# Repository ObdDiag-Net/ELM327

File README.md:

ELM327 adapter and firmware based on PIC18F25K80
==========================================

See http://www.obddiag.net/elm327.html project page for details.

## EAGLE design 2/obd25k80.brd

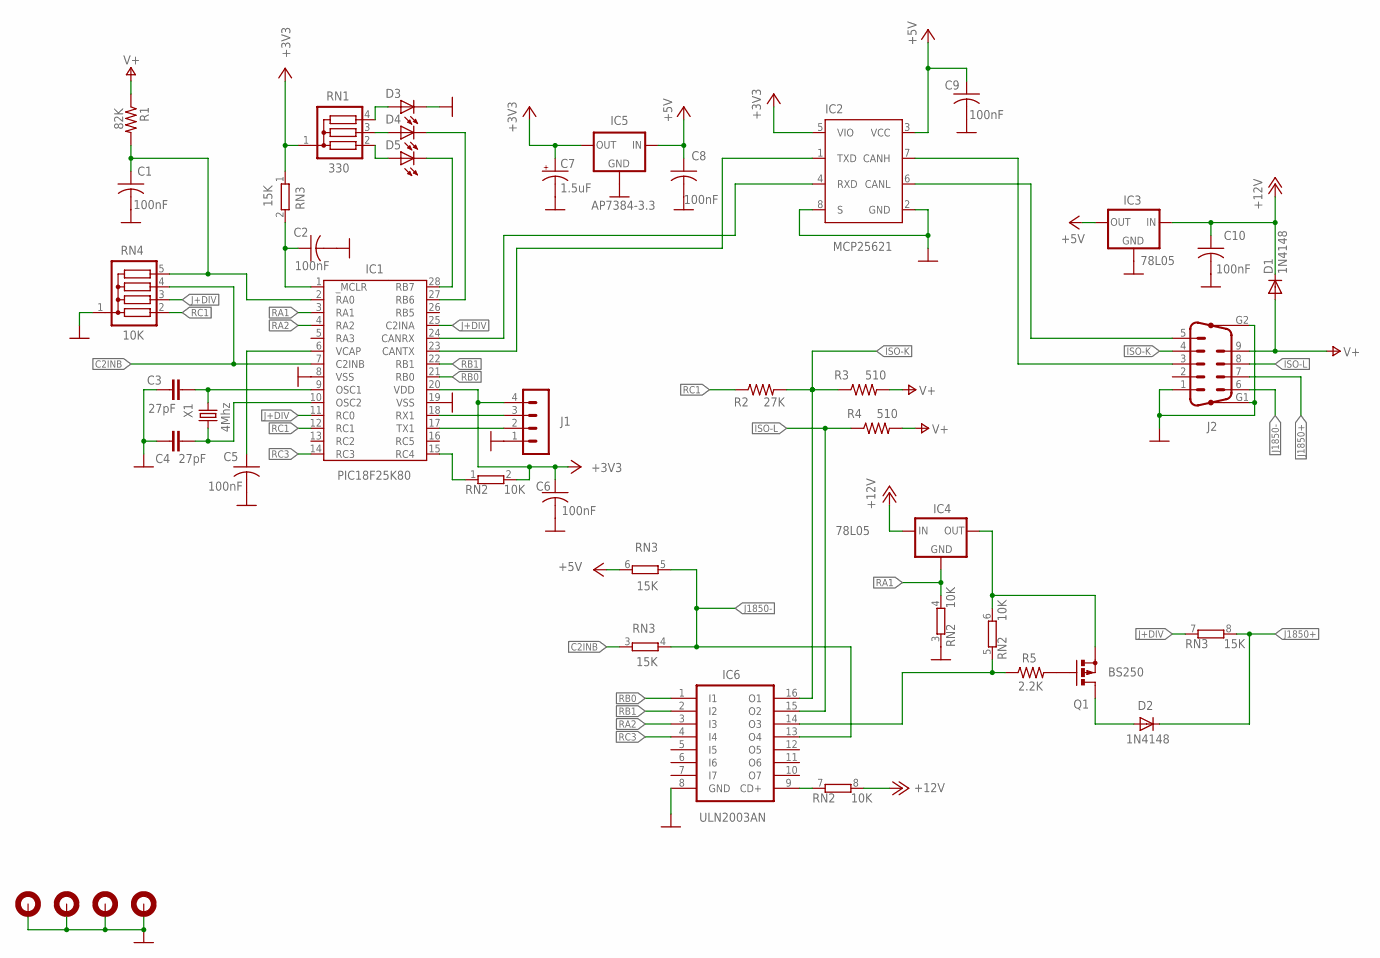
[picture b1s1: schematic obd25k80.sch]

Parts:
C1, C2, C5, C6, C8, C9, C10: 100nF; C050-025X075
C3, C4: 27pF; C2.5-2
C7: 1.5uF; E2,5-5
D1, D2: 1N4148; D035-10M
D3, D4, D5: LED5MM
H1, H2, H3, H4: MOUNT-PAD-ROUND2.8; 2,8-PAD
IC1: PIC18F25K80; DIL28
IC2: MCP25621; DIL8
IC3, IC4: 78L05; 78LXX
IC5: AP7384-3.3; TO92
IC6: ULN2003AN; DIL16
J1: MA04-1
J2: DB9-M; M09HP
Q1: BS250; SOT54E
R1: 82K; 0207/10
R2: 27K; 0207/10
R3, R4: 510; 0207/10
R5: 2.2K; 0207/10
RN1: 330; SIL4
RN2: 10K; SIL8
RN3: 15K; SIL8
RN4: 10K; SIL5
X1: 4Mhz; HC49/S

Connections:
+3V3: C6.1, C7.+, IC1.20 (VDD), IC2.5 (VIO), IC5.3 (OUT), J1.4, RN1.1, RN2.2, RN3.1
+5V: C8.1, C9.1, IC2.3 (VCC), IC3.OUT, IC5.1 (IN), RN3.6 (2)
+12V: C10.1, D1.C, IC3.IN, IC4.IN, RN2.8 (2)
C2INB: IC1.7 (C2INB), RN3.3 (1), RN4.4
CAN-H: IC2.7 (CANH), J2.3
CAN-L: IC2.6 (CANL), J2.5
GND: C1.2, C2.2, C3.1, C4.2, C5.2, C6.2, C7.-, C8.2, C9.2, C10.2, D3.K (C), H1.B2,8, H2.B2,8, H3.B2,8, H4.B2,8, IC1.8 (VSS), IC1.19 (VSS), IC2.2 (GND), IC2.8 (S), IC3.GND, IC5.2 (GND), IC6.8 (GND), J1.1, J2.1, J2.G1, J2.G2, RN2.3 (1), RN4.1
ISO-K: IC6.16 (O1), J2.4, R2.2, R3.1
ISO-L: IC6.15 (O2), J2.8, R4.1
J1850+: D2.C, J2.7, RN3.8 (2)
J1850-: IC6.13 (O4), J2.6, RN3.4 (2), RN3.5 (1)
J+DIV: IC1.11 (RC0), IC1.25 (C2INA), RN3.7 (1), RN4.3
unnamed: D5.A, RN1.2
unnamed: D5.K (C), IC1.28 (RB7)
unnamed: IC1.15 (RC4), RN2.1
unnamed: IC6.9 (CD+), RN2.7 (1)
unnamed: D4.A, RN1.3
unnamed: D3.A, RN1.4
unnamed: C2.1, IC1.1 (_MCLR), RN3.2
unnamed: D2.A, Q1.D
unnamed: C1.1, IC1.2 (RA0), R1.2, RN4.5
unnamed: Q1.G, R5.2
unnamed: D4.K (C), IC1.27 (RB6)
unnamed: C5.1, IC1.6 (VCAP)
unnamed: IC1.18 (RX1), J1.3
unnamed: IC1.24 (CANRX), IC2.4 (RXD)
unnamed: IC1.17 (TX1), J1.2
unnamed: C3.2, IC1.9 (OSC1), X1.2
unnamed: IC1.23 (CANTX), IC2.1 (TXD)
unnamed: IC6.14 (O3), R5.1, RN2.5 (1)
unnamed: IC4.OUT, Q1.S, RN2.6 (2)
unnamed: C4.1, IC1.10 (OSC2), X1.1
RA1: IC1.3 (RA1), IC4.GND, RN2.4 (2)
RA2: IC1.4 (RA2), IC6.3 (I3)
RB0: IC1.21 (RB0), IC6.1 (I1)
RB1: IC1.22 (RB1), IC6.2 (I2)
RC1: IC1.12 (RC1), R2.1, RN4.2
RC3: IC1.14 (RC3), IC6.4 (I4)
V+: D1.A, J2.9, R1.1, R3.2, R4.2

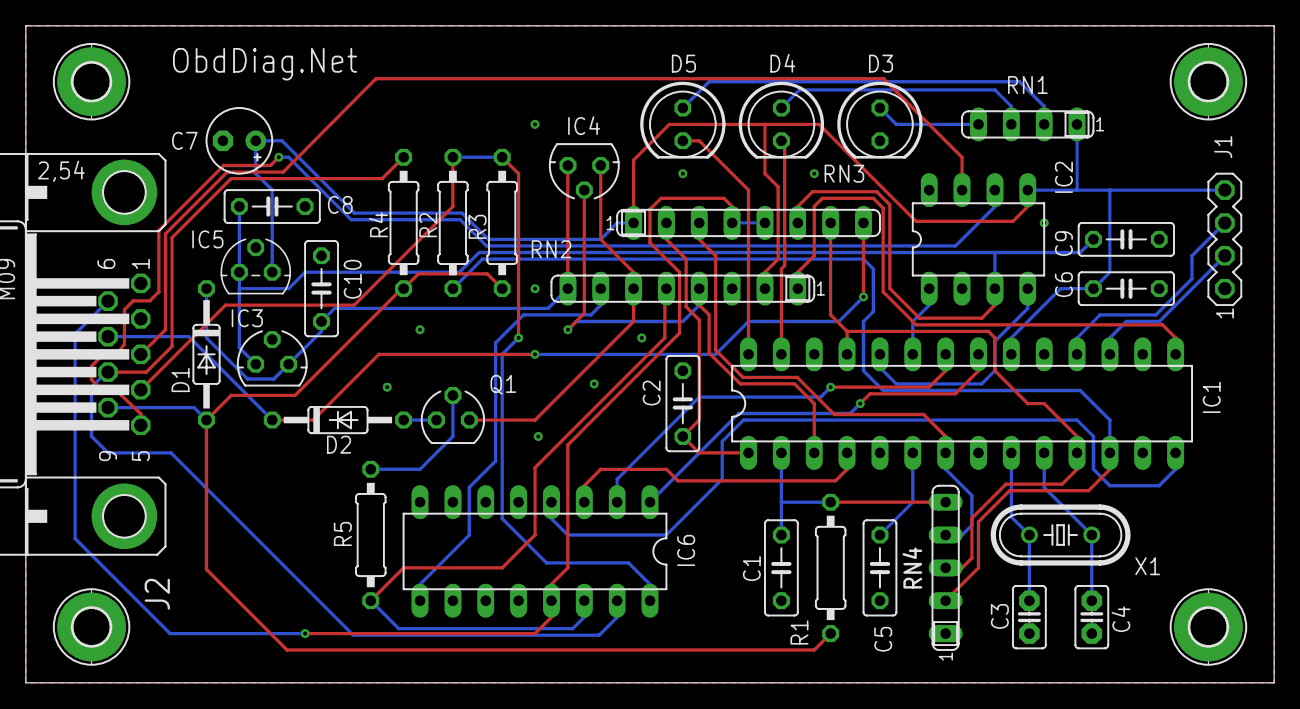
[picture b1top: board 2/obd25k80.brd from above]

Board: 2 copper layers, 96.5 x 50.8 mm, 38 parts (0 on the bottom side), 39 nets.

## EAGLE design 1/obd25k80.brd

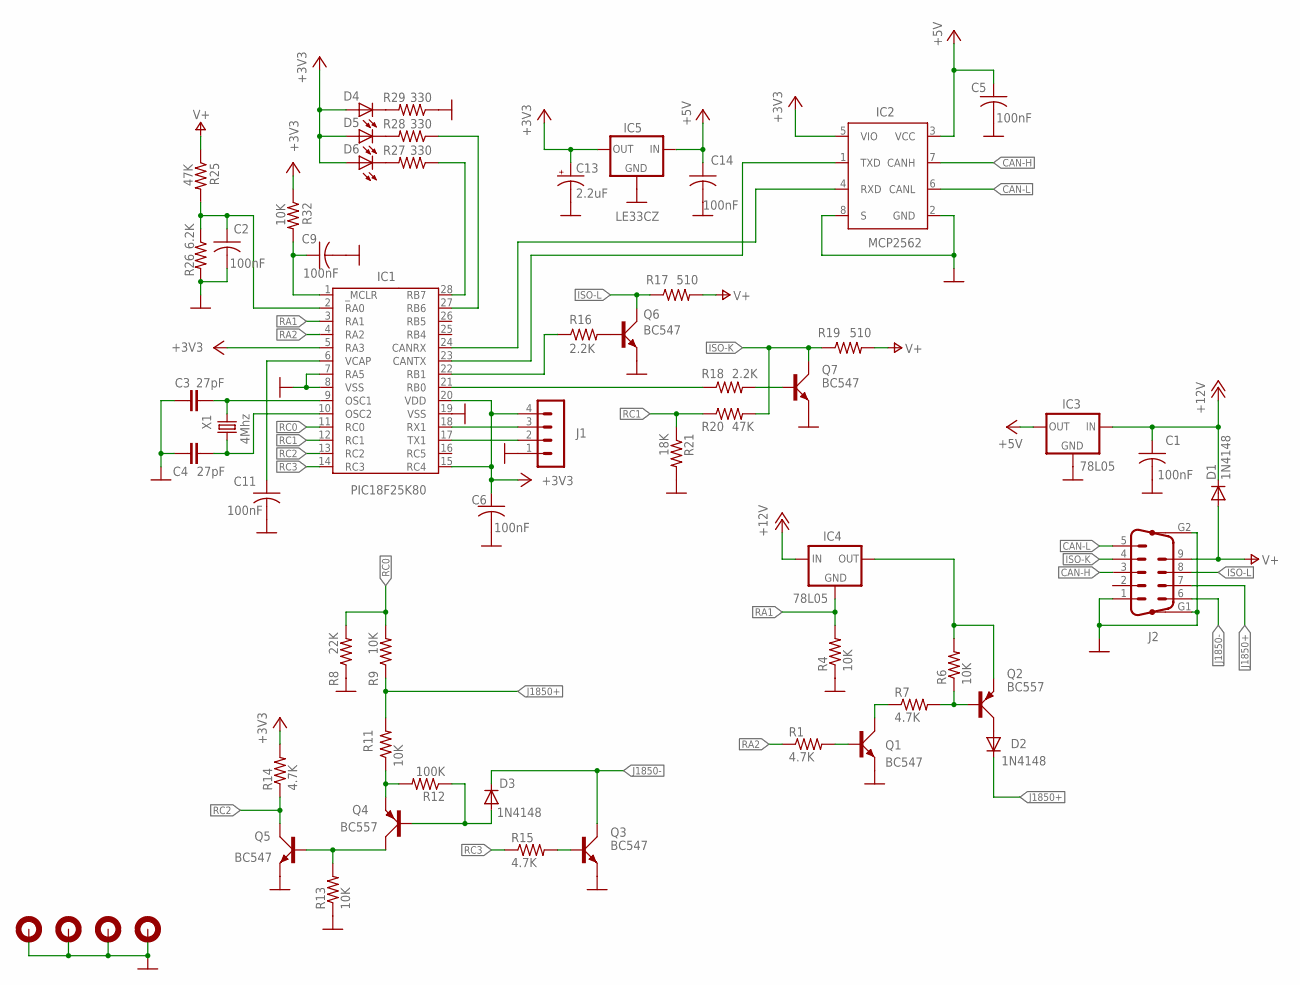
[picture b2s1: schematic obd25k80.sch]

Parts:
C1, C2, C5, C6, C9, C11, C14: 100nF; C050-025X075
C3, C4: 27pF; C2.5-2
C13: 2.2uF; E2,5-5
D1, D2, D3: 1N4148; D035-10M
D4, D5, D6: LED5MM
H1, H2, H3, H4: MOUNT-PAD-ROUND2.8; 2,8-PAD
IC1: PIC18F25K80; DIL28
IC2: MCP2562; DIL8
IC3, IC4: 78L05; 78LXX
IC5: LE33CZ; 78LXX
J1: MA04-1
J2: DB9-M; M09HP
Q1, Q3, Q5, Q6, Q7: BC547; SOT54A
Q2, Q4: BC557; SOT54A
R1, R7, R14, R15: 4.7K; 0207/10
R4, R6, R9, R11, R13, R32: 10K; 0207/10
R8: 22K; 0207/10
R12: 100K; 0207/10
R16, R18: 2.2K; 0207/10
R17, R19: 510; 0207/10
R20, R25: 47K; 0207/10
R21: 18K; 0207/10
R26: 6.2K; 0207/10
R27, R28, R29: 330; 0207/10
X1: 4Mhz; HC49/S

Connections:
+3V3: C6.1, C13.+, D4.A, D5.A, D6.A, IC1.5 (RA3), IC1.15 (RC4), IC1.20 (VDD), IC2.5 (VIO), IC5.OUT, J1.4, R14.2, R32.1
+5V: C5.1, C14.1, IC2.3 (VCC), IC3.OUT, IC5.IN
+12V: C1.1, D1.C, IC3.IN, IC4.IN
CAN-H: IC2.7 (CANH), J2.3
CAN-L: IC2.6 (CANL), J2.5
GND: C1.2, C2.2, C3.1, C4.2, C5.2, C6.2, C9.2, C11.2, C13.-, C14.2, H1.B2,8, H2.B2,8, H3.B2,8, H4.B2,8, IC1.7 (RA5), IC1.8 (VSS), IC1.19 (VSS), IC2.2 (GND), IC2.8 (S), IC3.GND, IC5.GND, J1.1, J2.1, J2.G1, J2.G2, Q1.E, Q3.E, Q5.E, Q6.E, Q7.E, R4.1, R8.1, R13.1, R21.2, R26.2, R29.1
ISO-K: J2.4, Q7.C, R19.1, R20.2
ISO-L: J2.8, Q6.C, R17.1
J1850+: D2.C, J2.7, R9.1, R11.2
J1850-: D3.C, J2.6, Q3.C
unnamed: D4.K (C), R29.2
unnamed: IC1.28 (RB7), R27.1
unnamed: D5.K (C), R28.2
unnamed: C9.1, IC1.1 (_MCLR), R32.2
unnamed: IC1.22 (RB1), R16.1
unnamed: D6.K (C), R27.2
unnamed: IC1.27 (RB6), R28.1
unnamed: C11.1, IC1.6 (VCAP)
unnamed: Q6.B, R16.2
unnamed: IC1.18 (RX1), J1.3
unnamed: IC1.24 (CANRX), IC2.4 (RXD)
unnamed: IC1.17 (TX1), J1.2
unnamed: IC1.21 (RB0), R18.1
unnamed: C3.2, IC1.9 (OSC1), X1.2
unnamed: Q3.B, R15.2
unnamed: IC1.23 (CANTX), IC2.1 (TXD)
unnamed: Q7.B, R18.2
unnamed: Q1.C, R7.1
unnamed: C2.1, IC1.2 (RA0), R25.2, R26.1
unnamed: Q1.B, R1.2
unnamed: Q2.B, R6.1, R7.2
unnamed: IC4.OUT, Q2.E, R6.2
unnamed: D2.A, Q2.C
unnamed: Q4.E, R11.1, R12.2
unnamed: D3.A, Q4.B, R12.1
unnamed: Q4.C, Q5.B, R13.2
unnamed: C4.1, IC1.10 (OSC2), X1.1
RA1: IC1.3 (RA1), IC4.GND, R4.2
RA2: IC1.4 (RA2), R1.1
RC0: IC1.11 (RC0), R8.2, R9.2
RC1: IC1.12 (RC1), R20.1, R21.1
RC2: IC1.13 (RC2), Q5.C, R14.1
RC3: IC1.14 (RC3), R15.1
V+: D1.A, J2.9, R17.2, R19.2, R25.1

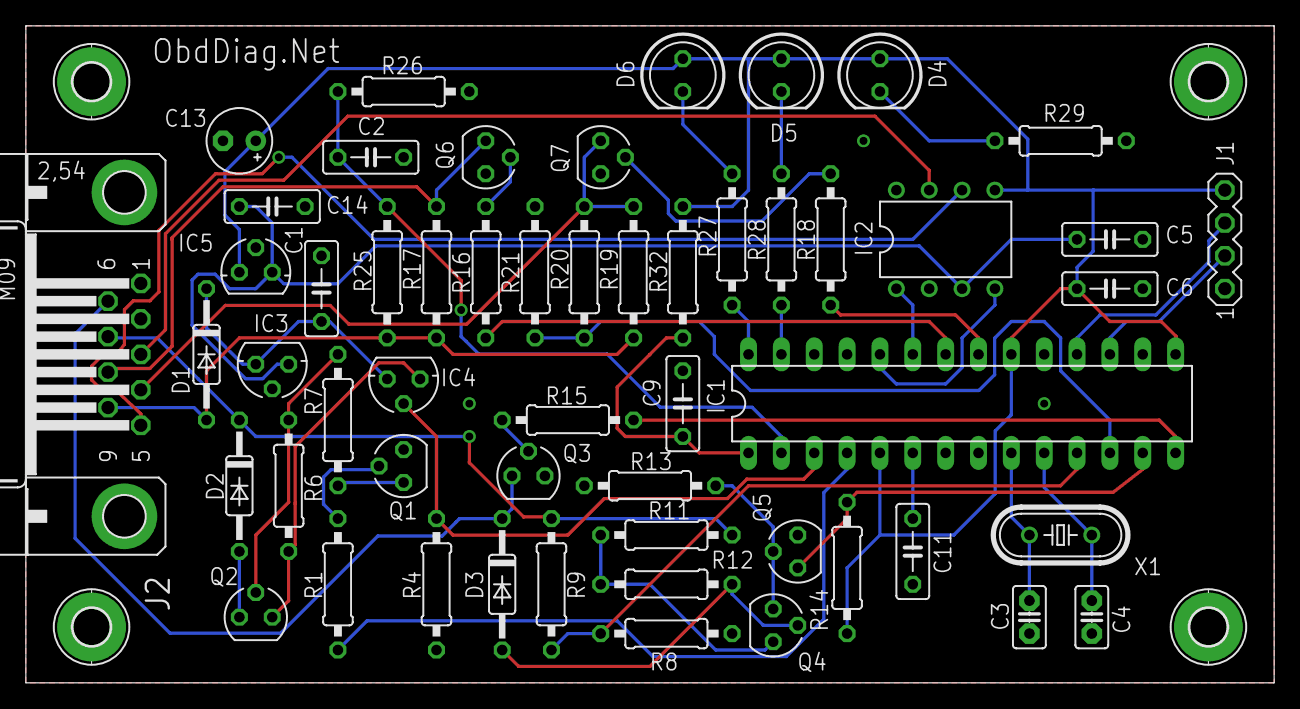
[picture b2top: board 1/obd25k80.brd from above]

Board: 2 copper layers, 96.5 x 50.8 mm, 58 parts (0 on the bottom side), 44 nets.

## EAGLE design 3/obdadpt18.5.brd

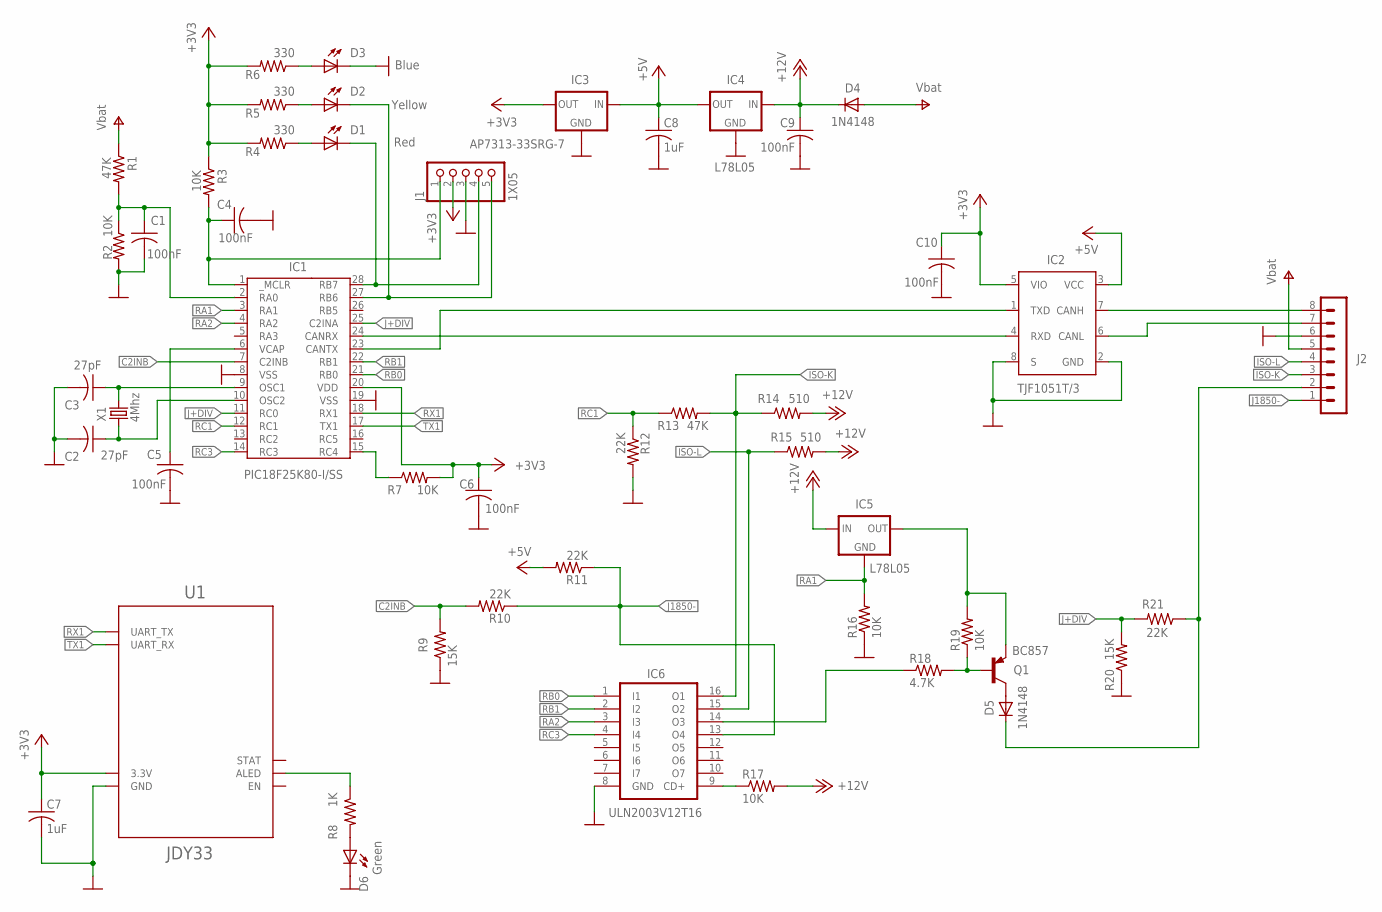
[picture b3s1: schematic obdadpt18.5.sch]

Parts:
C1, C4, C5, C6, C9, C10: 100nF; C0805
C2, C3: 27pF; C0805
C7, C8: 1uF; C0805
D1: Red; CHIPLED_0805
D2: Yellow; CHIPLED_0805
D3: Blue; CHIPLED_0805
D4, D5: 1N4148; SOD123
D6: Green; CHIPLED_0805
IC1: PIC18F25K80-I/SS; SSOP28DB
IC2: TJF1051T/3; SO-8
IC3: AP7313-33SRG-7; SOT23
IC4, IC5: L78L05; SOT89R
IC6: ULN2003V12T16; TSSOP16
J1: 1X05
J2: MA08-1
Q1: BC857; SOT23-BEC
R1, R13: 47K; R0805
R2, R3, R7, R16, R17, R19: 10K; R0805
R4, R5, R6: 330; R0805
R8: 1K; R0805
R9, R20: 15K; R0805
R10, R11, R12, R21: 22K; R0805
R14, R15: 510; R1206
R18: 4.7K; R0805
U1: JDY33
X1: 4Mhz; SM49

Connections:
+3V3: C6.1, C7.1, C10.1, IC1.20 (VDD), IC2.5 (VIO), IC3.2 (OUT), J1.2, R3.1, R4.2, R5.2, R6.2, R7.2, U1.12 (3.3V)
+5V: C8.1, IC2.3 (VCC), IC3.3 (IN), IC4.2 (OUT), R11.2
+12V: C9.1, D4.C, IC4.1 (IN), IC5.1 (IN), R14.2, R15.2, R17.2
C2INB: IC1.7 (C2INB), R9.2, R10.2
CAN-H: IC2.7 (CANH), J2.8
CAN-L: IC2.6 (CANL), J2.7
GND: C1.2, C2.2, C3.2, C4.2, C5.2, C6.2, C7.2, C8.2, C9.2, C10.2, D3.C, D6.C, IC1.8 (VSS), IC1.19 (VSS), IC2.2 (GND), IC2.8 (S), IC3.1 (GND), IC4.4 (GND), IC6.8 (GND), J1.3, J2.6, R2.2, R9.1, R12.2, R16.1, R20.1, U1.13 (GND)
ISO-K: IC6.16 (O1), J2.3, R13.2, R14.1
ISO-L: IC6.15 (O2), J2.4, R15.1
J1850+: D5.C, J2.2, R21.1
J1850-: IC6.13 (O4), J2.1, R10.1, R11.1
J+DIV: IC1.11 (RC0), IC1.25 (C2INA), R20.2, R21.2
unnamed: D6.A, R8.2
unnamed: D5.A, Q1.C
unnamed: D1.A, R4.1
unnamed: R8.1, U1.16 (ALED)
unnamed: D1.C, IC1.28 (RB7), J1.4
unnamed: D2.A, R5.1
unnamed: D3.A, R6.1
unnamed: D2.C, IC1.27 (RB6), J1.5
unnamed: IC1.24 (CANRX), IC2.4 (RXD)
unnamed: C5.1, IC1.6 (VCAP)
unnamed: C4.1, IC1.1 (_MCLR), J1.1, R3.2
unnamed: IC1.15 (RC4), R7.1
unnamed: C3.1, IC1.9 (OSC1), X1.1
unnamed: IC6.9 (CD+), R17.1
unnamed: IC1.23 (CANTX), IC2.1 (TXD)
unnamed: IC6.14 (O3), R18.1
unnamed: C1.1, IC1.2 (RA0), R1.2, R2.1
unnamed: Q1.B, R18.2, R19.1
unnamed: IC5.2 (OUT), Q1.E, R19.2
unnamed: C2.1, IC1.10 (OSC2), X1.2
RA1: IC1.3 (RA1), IC5.4 (GND), R16.2
RA2: IC1.4 (RA2), IC6.3 (I3)
RB0: IC1.21 (RB0), IC6.1 (I1)
RB1: IC1.22 (RB1), IC6.2 (I2)
RC1: IC1.12 (RC1), R12.1, R13.1
RC3: IC1.14 (RC3), IC6.4 (I4)
RX1: IC1.18 (RX1), U1.1 (UART_TX)
TX1: IC1.17 (TX1), U1.2 (UART_RX)
V+: D4.A, J2.5, R1.1

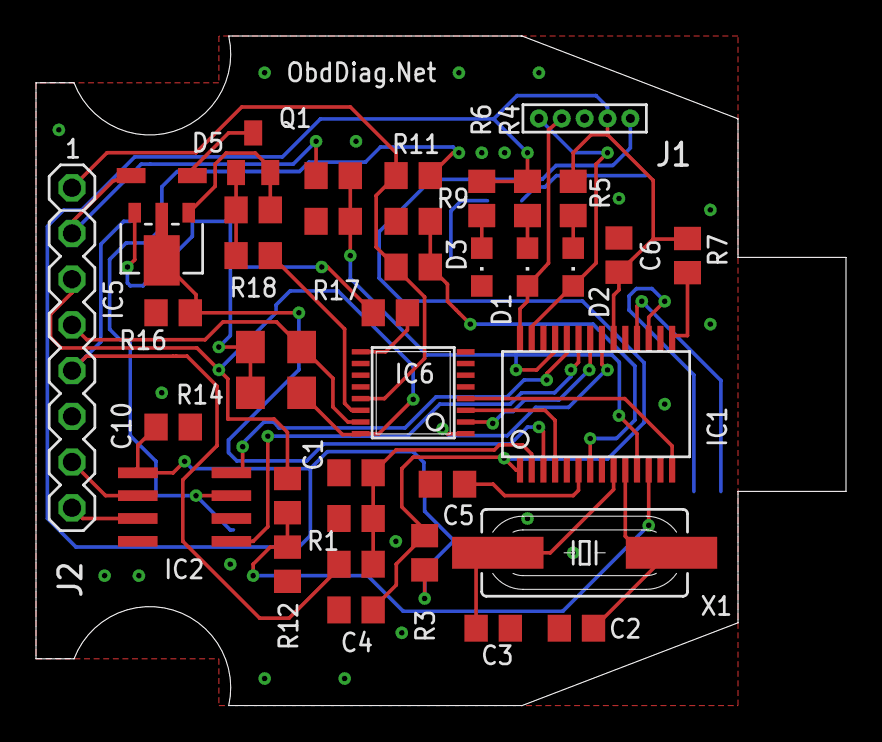
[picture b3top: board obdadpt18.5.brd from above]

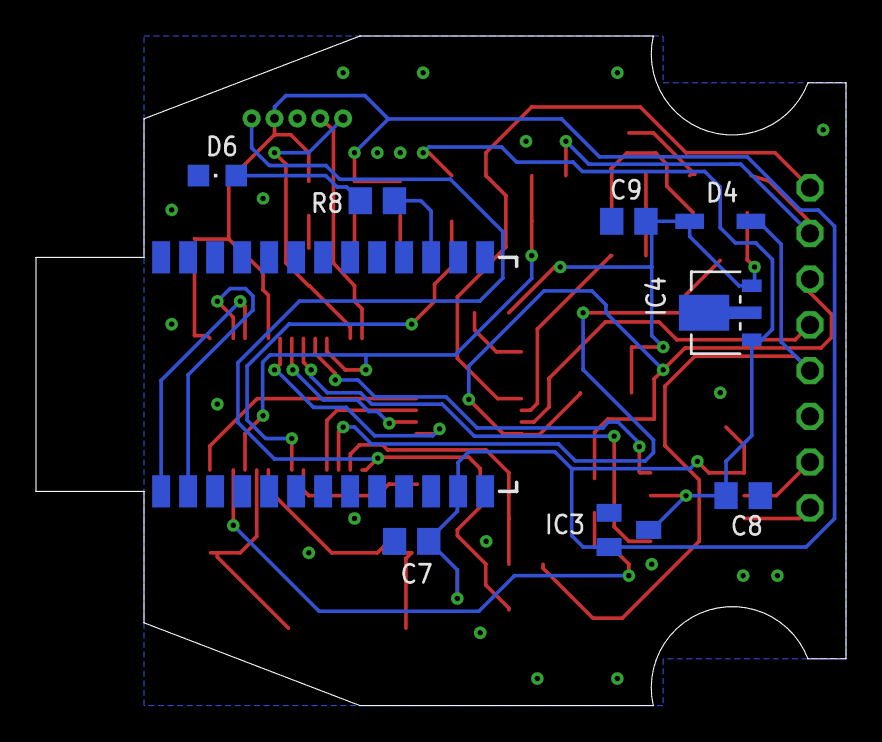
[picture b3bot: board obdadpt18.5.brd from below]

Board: 2 copper layers, 45.0 x 37.2 mm, 48 parts (9 on the bottom side), 41 nets.

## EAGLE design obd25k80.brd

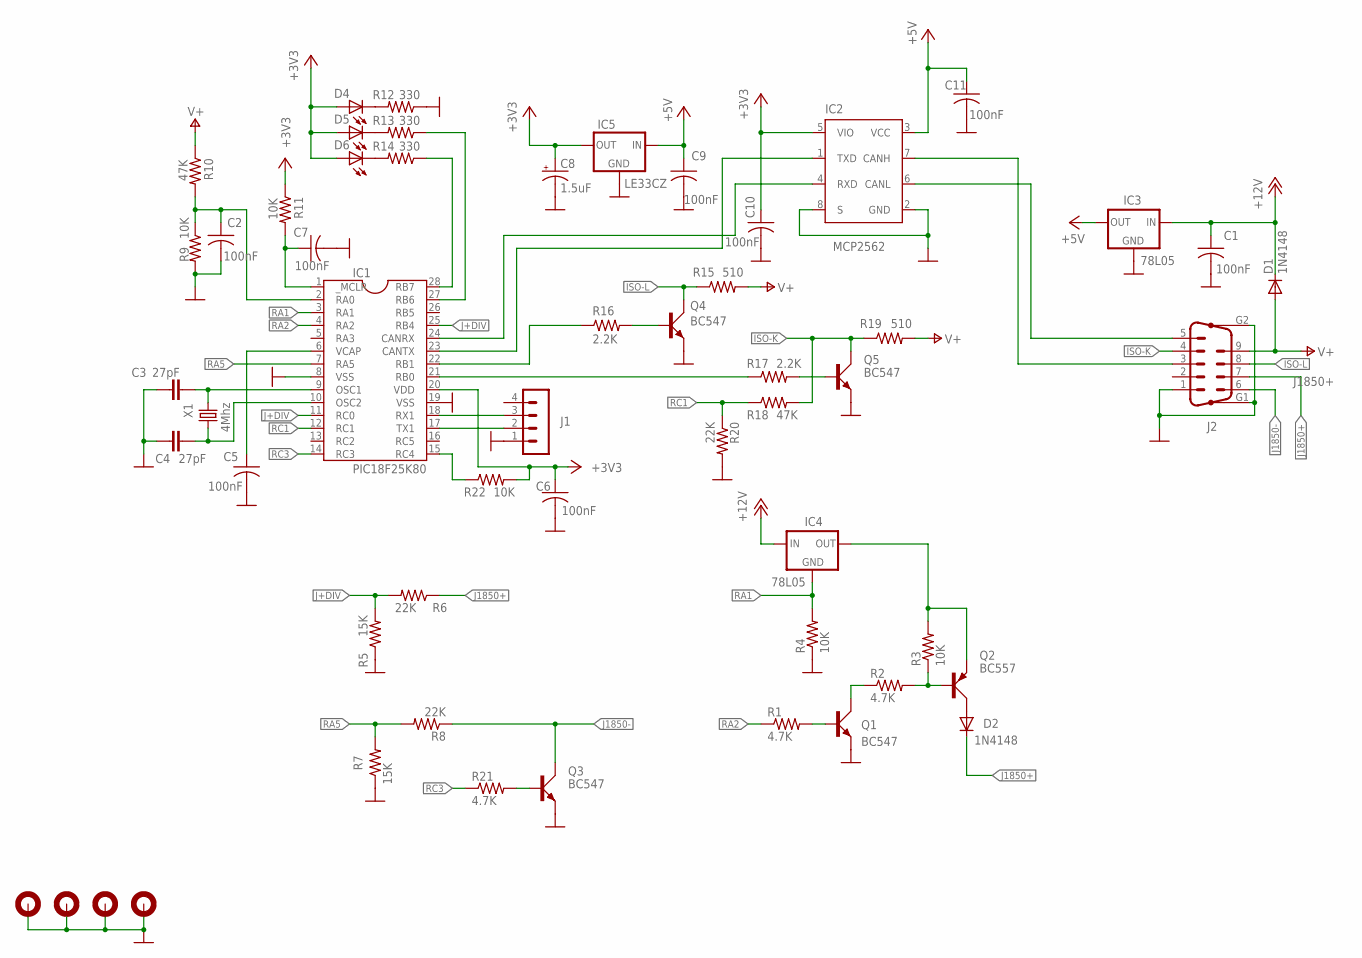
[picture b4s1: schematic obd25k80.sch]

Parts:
C1, C2, C5, C6, C7, C9, C10, C11: 100nF; C050-025X075
C3, C4: 27pF; C2.5-2
C8: 1.5uF; E2,5-5
D1, D2: 1N4148; D035-10M
D4, D5, D6: LED5MM
H1, H2, H3, H4: MOUNT-PAD-ROUND2.8; 2,8-PAD
IC1: PIC18F25K80; DIL28
IC2: MCP2562; DIL8
IC3, IC4: 78L05; 78LXX
IC5: LE33CZ; 78LXX
J1: MA04-1
J2: DB9-M; M09HP
Q1, Q3, Q4, Q5: BC547; SOT54A
Q2: BC557; SOT54A
R1, R2, R21: 4.7K; 0207/10
R3, R4, R9, R11, R22: 10K; 0207/10
R5, R7: 15K; 0207/10
R6, R8, R20: 22K; 0207/10
R10, R18: 47K; 0207/10
R12, R13, R14: 330; 0207/10
R15, R19: 510; 0207/10
R16, R17: 2.2K; 0207/10
X1: 4Mhz; HC49/S

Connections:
+3V3: C6.1, C8.+, C10.1, D4.A, D5.A, D6.A, IC1.20 (VDD), IC2.5 (VIO), IC5.OUT, R11.1, R22.2
+5V: C9.1, C11.1, IC2.3 (VCC), IC3.OUT, IC5.IN
+12V: C1.1, D1.C, IC3.IN, IC4.IN
CAN-H: IC2.7 (CANH), J2.3
CAN-L: IC2.6 (CANL), J2.5
GND: C1.2, C2.2, C3.1, C4.2, C5.2, C6.2, C7.2, C8.-, C9.2, C10.2, C11.2, H1.B2,8, H2.B2,8, H3.B2,8, H4.B2,8, IC1.8 (VSS), IC1.19 (VSS), IC2.2 (GND), IC2.8 (S), IC3.GND, IC5.GND, J1.1, J2.1, J2.G1, J2.G2, Q1.E, Q3.E, Q4.E, Q5.E, R4.1, R5.1, R7.1, R9.2, R12.1, R20.2
ISO-K: J2.4, Q5.C, R18.2, R19.1
ISO-L: J2.8, Q4.C, R15.1
J1850+: D2.C, J2.7, R6.1
J1850-: J2.6, Q3.C, R8.1
J+DIV: IC1.11 (RC0), IC1.25 (RB4), R5.2, R6.2
unnamed: D4.K (C), R12.2
unnamed: IC1.28 (RB7), R14.1
unnamed: IC1.15 (RC4), R22.1
unnamed: D5.K (C), R13.2
unnamed: C7.1, IC1.1 (_MCLR), R11.2
unnamed: IC1.22 (RB1), R16.1
unnamed: D6.K (C), R14.2
unnamed: IC1.27 (RB6), R13.1
unnamed: C5.1, IC1.6 (VCAP)
unnamed: Q4.B, R16.2
unnamed: IC1.18 (RX1), J1.3
unnamed: IC1.24 (CANRX), IC2.4 (RXD)
unnamed: IC1.17 (TX1), J1.2
unnamed: IC1.21 (RB0), R17.1
unnamed: C3.2, IC1.9 (OSC1), X1.2
unnamed: Q3.B, R21.2
unnamed: IC1.23 (CANTX), IC2.1 (TXD)
unnamed: Q5.B, R17.2
unnamed: Q1.C, R2.1
unnamed: C2.1, IC1.2 (RA0), R9.1, R10.2
unnamed: Q1.B, R1.2
unnamed: Q2.B, R2.2, R3.1
unnamed: IC4.OUT, Q2.E, R3.2
unnamed: D2.A, Q2.C
unnamed: C4.1, IC1.10 (OSC2), X1.1
RA1: IC1.3 (RA1), IC4.GND, R4.2
RA2: IC1.4 (RA2), R1.1
RA5: IC1.7 (RA5), R7.2, R8.2
RC1: IC1.12 (RC1), R18.1, R20.1
RC3: IC1.14 (RC3), R21.1
V+: D1.A, J2.9, R10.1, R15.2, R19.2

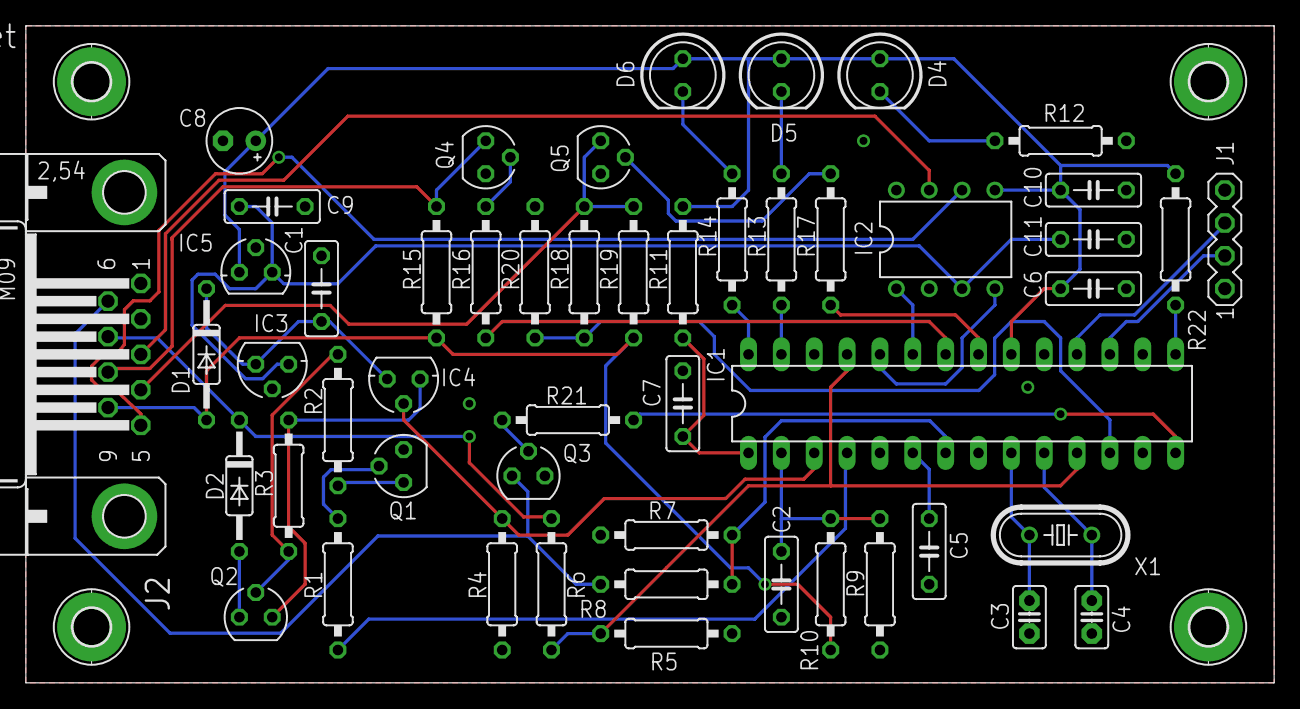
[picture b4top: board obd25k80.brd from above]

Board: 2 copper layers, 96.5 x 50.8 mm, 55 parts (0 on the bottom side), 42 nets.

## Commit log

2022-04-16 Initial release
2022-04-18 Cleanup
2022-04-18 Added simplified schematic
2022-04-18 Libraty updated for PIC18F25K80
2022-04-19 Fixed minor issues
2022-04-20 Reimplemented with ULN2003
2022-04-23 A few optimizations
2022-04-24 Added .pdf
2022-04-30 Removed excessive capacitor
2022-04-30 Another 3.3V LDO
2022-08-19 Updated with resistor arrays
